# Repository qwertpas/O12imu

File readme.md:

## Compact 6DOF sensor fusion IMU for RS485 bus

Intended to work with [squirrelbrain](https://github.com/qwertpas/squirrelbrain) as part of the [Pintobotics](https://pintobotics.substack.com) project.

IMU: [LSM6DSV](https://www.st.com/en/mems-and-sensors/lsm6dsv.html)

MCU: [STM32L011F4U](https://www.digikey.com/en/products/detail/stmicroelectronics/STM32L011F4U6TR/6166960)

Size: 12.5mm x 12.5mm

Mounting: 4x M2 on 12mm diameter circle 

Connection: 2x 4pin 0.5mm pitch FFC for power and RS485 communication (daisy chainable)

Alternate connection: I2C and interrupt solder pads, aux GPIO/ADC

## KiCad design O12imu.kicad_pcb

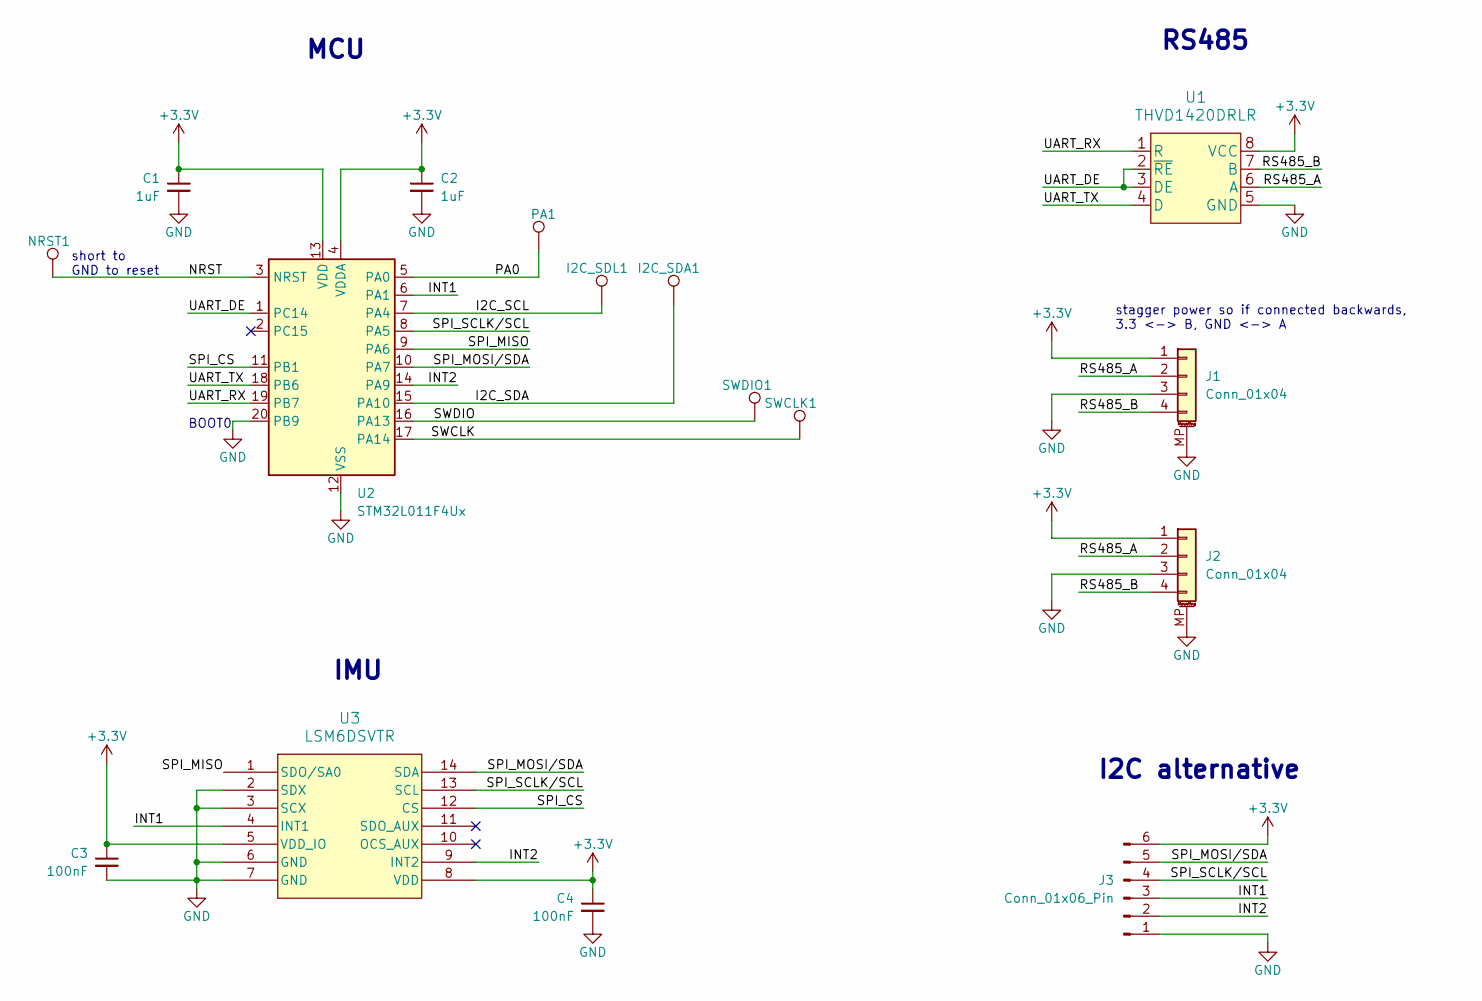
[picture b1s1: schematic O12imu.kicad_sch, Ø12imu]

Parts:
C1, C2: 1uF; C_0402_1005Metric; MPN CL05A105KA5NQNC
C3, C4: 100nF; C_0402_1005Metric
I2C_SDA1, I2C_SDL1: TestPoint; TestPoint_Pad_Rect
J1, J2: Conn_01x04; TE_2328702-4
J3: Conn_01x06_Pin; FFC_0.5mm_6p
NRST1: TestPoint; TestPoint_Pad_Rect
PA1: TestPoint; TestPoint_Pad_Rect
SWCLK1: TestPoint; TestPoint_Pad_Rect
SWDIO1: TestPoint; TestPoint_Pad_Rect
U1: THVD1420DRLR; THVD1420DRLR_SOT-585; MPN THVD1420DRLR
U2: STM32L011F4Ux; ST_UFQFPN-20_3x3mm_P0.5mm
U3: LSM6DSVTR; LGA14-L_2P59X3P1X0P5_STM

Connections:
+3.3V: C1.1, C2.1, C3.1, C4.1, J1.1, J2.1, J3.6, U1.8 (VCC), U2.4 (VDDA), U2.13 (VDD), U3.5 (VDD_IO), U3.8 (VDD)
/I2C_SCL: I2C_SDL1.1, U2.7 (PA4)
/I2C_SDA: I2C_SDA1.1, U2.15 (PA10)
/INT1: J3.3, U2.6 (PA1), U3.4 (INT1)
/INT2: J3.2, U2.14 (PA9), U3.9 (INT2)
/NRST: NRST1.1, U2.3 (NRST)
/PA0: PA1.1, U2.5 (PA0)
/RS485_A: J1.2, J2.2, U1.6 (A)
/RS485_B: J1.4, J2.4, U1.7 (B)
/SPI_CS: U2.11 (PB1), U3.12 (CS)
/SPI_MISO: U2.9 (PA6), U3.1 (SDO/SA0)
/SPI_MOSI/SDA: J3.5, U2.10 (PA7), U3.14 (SDA)
/SPI_SCLK/SCL: J3.4, U2.8 (PA5), U3.13 (SCL)
/SWCLK: SWCLK1.1, U2.17 (PA14)
/SWDIO: SWDIO1.1, U2.16 (PA13)
/UART_DE: U1.2 (~RE), U1.3 (DE), U2.1 (PC14)
/UART_RX: U1.1 (R), U2.19 (PB7)
/UART_TX: U1.4 (D), U2.18 (PB6)
GND: C1.2, C2.2, C3.2, C4.2, J1.3, J1.MP (MountPin), J2.3, J2.MP (MountPin), J3.1, U1.5 (GND), U2.12 (VSS), U2.20 (PB9), U3.2 (SDX), U3.3 (SCX), U3.6 (GND), U3.7 (GND)

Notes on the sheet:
I2C alternative
BOOT0
stagger power so if connected backwards, 3.3 <-> B, GND <-> A
MCU
IMU
short to GND to reset
RS485

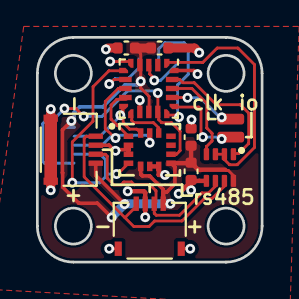
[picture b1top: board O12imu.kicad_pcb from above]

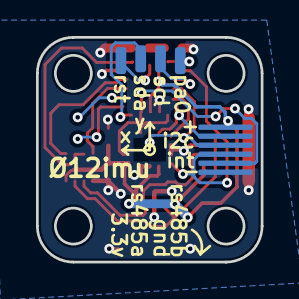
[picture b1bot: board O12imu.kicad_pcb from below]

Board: 2 copper layers, 12.5 x 12.5 mm, 16 parts (5 on the bottom side), 19 nets.

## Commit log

2024-03-10 readme, bom, schematic pdf
2024-03-10 shifted cap pos, readme details
2024-04-15 Add MIT License
